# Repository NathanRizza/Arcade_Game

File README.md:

# Arcade_Game
Arduino based arcade game where you need to stop a blinking light in the middle of a set of five blinking lights.

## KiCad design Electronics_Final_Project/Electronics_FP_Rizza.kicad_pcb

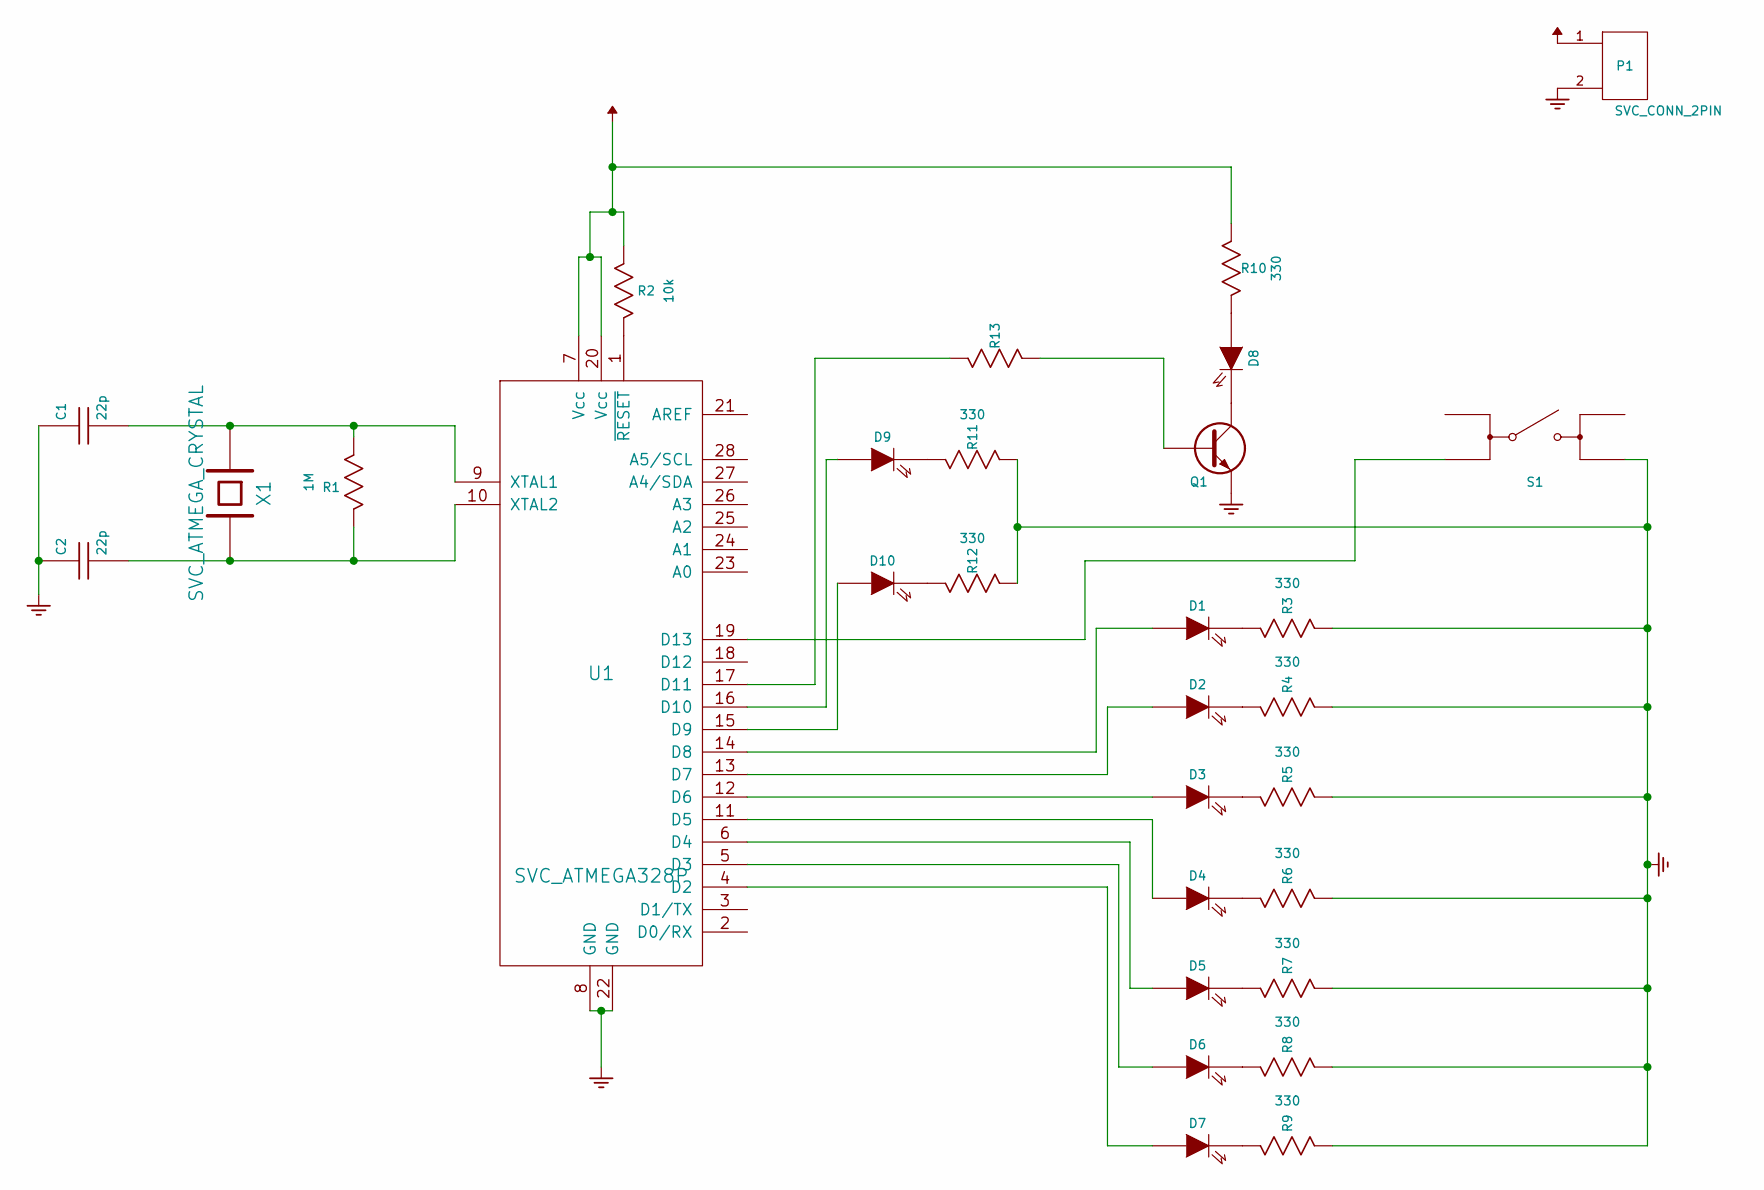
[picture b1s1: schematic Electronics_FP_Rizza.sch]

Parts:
C1, C2: 22p; SM1206
D1, D2, D3, D4, D5, D6, D7, D8, D9, D10: SVC_LED; SM1206
P1: SVC_CONN_2PIN; 2-PIN-Power
Q1: SVC_Q_MMBT3904L; SOT23
R1: 1M; SM1206
R2: 10k; SM1206
R3, R4, R5, R6, R7, R8, R9, R10, R11, R12: 330; SM1206
R13: SVC_R; SM1206
S1: SVC_BUTTON_SWITCH; BUTTON-SWITCH-SPST
U1: SVC_ATMEGA328P; SM_DIP28-300
X1: SVC_ATMEGA_CRYSTAL; crystal_16MHz

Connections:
GND: C1.1, C2.1, P1.2 (PM), Q1.2 (E), R3.1, R4.1, R5.1, R6.1, R7.1, R8.1, R9.1, R11.1, R12.1, S1.2, U1.8 (GND), U1.22 (GND)
unnamed: C1.2, R1.1, U1.9 (XTAL1), X1.1
unnamed: C2.2, R1.2, U1.10 (XTAL2), X1.2
unnamed: D1.1 (A), U1.14 (D8)
unnamed: D1.2 (K), R3.2
unnamed: D2.1 (A), U1.13 (D7)
unnamed: D2.2 (K), R4.2
unnamed: D3.1 (A), U1.12 (D6)
unnamed: D3.2 (K), R5.2
unnamed: D4.1 (A), U1.11 (D5)
unnamed: D4.2 (K), R6.2
unnamed: D5.1 (A), U1.6 (D4)
unnamed: D5.2 (K), R7.2
unnamed: D6.1 (A), U1.5 (D3)
unnamed: D6.2 (K), R8.2
unnamed: D7.1 (A), U1.4 (D2)
unnamed: D7.2 (K), R9.2
unnamed: D8.1 (A), R10.1
unnamed: D8.2 (K), Q1.3 (C)
unnamed: D9.1 (A), U1.16 (D10)
unnamed: D9.2 (K), R11.2
unnamed: D10.1 (A), U1.15 (D9)
unnamed: D10.2 (K), R12.2
unnamed: Q1.1 (B), R13.1
unnamed: R2.1, U1.1 (~RESET)
unnamed: R13.2, U1.17 (D11)
unnamed: S1.4, U1.19 (D13)
VCC: P1.1, R2.2, R10.2, U1.7 (Vcc), U1.20 (Vcc)

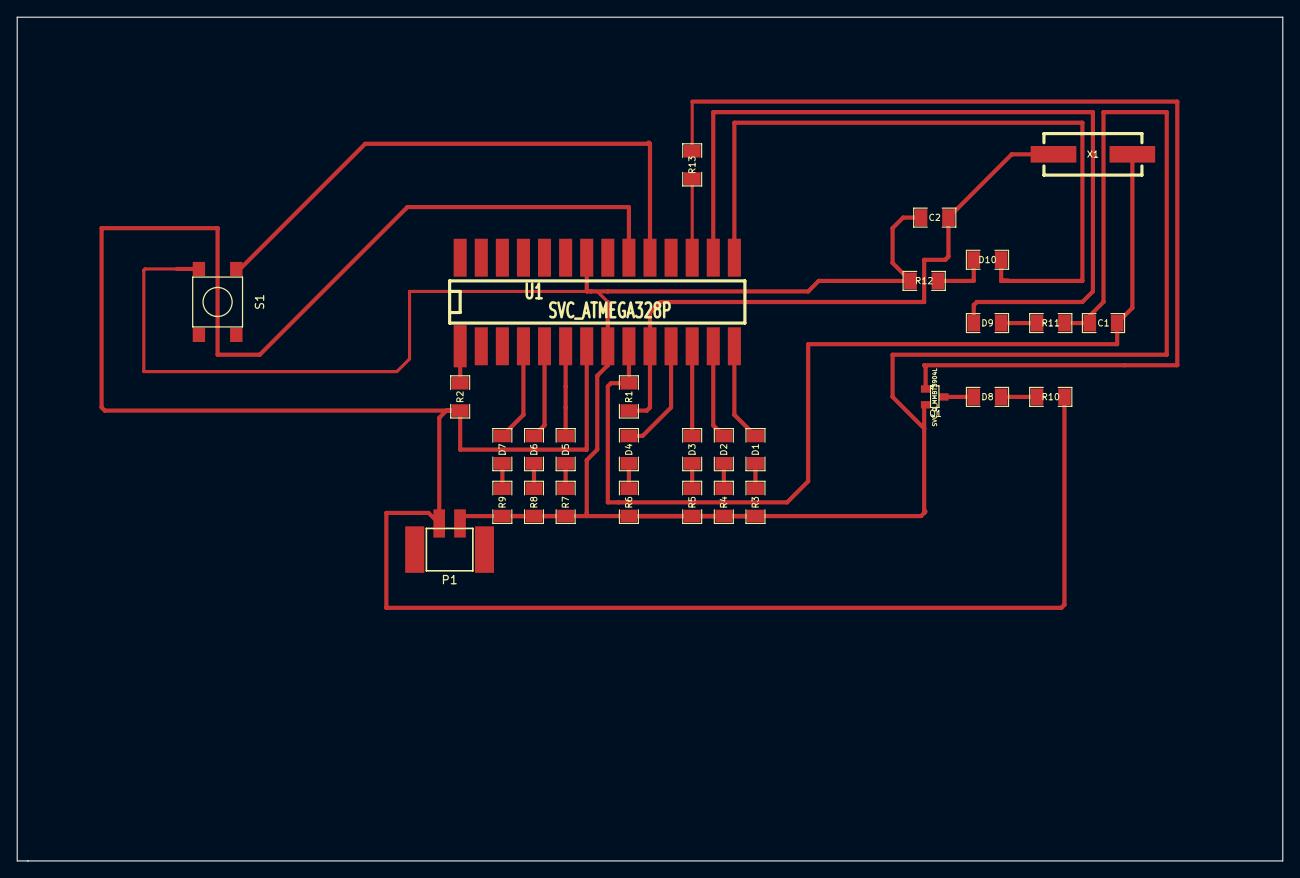
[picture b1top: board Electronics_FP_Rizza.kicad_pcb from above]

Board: 2 copper layers, 152.4 x 101.6 mm, 30 parts (0 on the bottom side), 28 nets.
